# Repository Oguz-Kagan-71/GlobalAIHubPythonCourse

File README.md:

# GlobalAIHubPythonCourse
https://github.com/globalaihub/gaih-students-repo-example/blob/main/img/logo.png

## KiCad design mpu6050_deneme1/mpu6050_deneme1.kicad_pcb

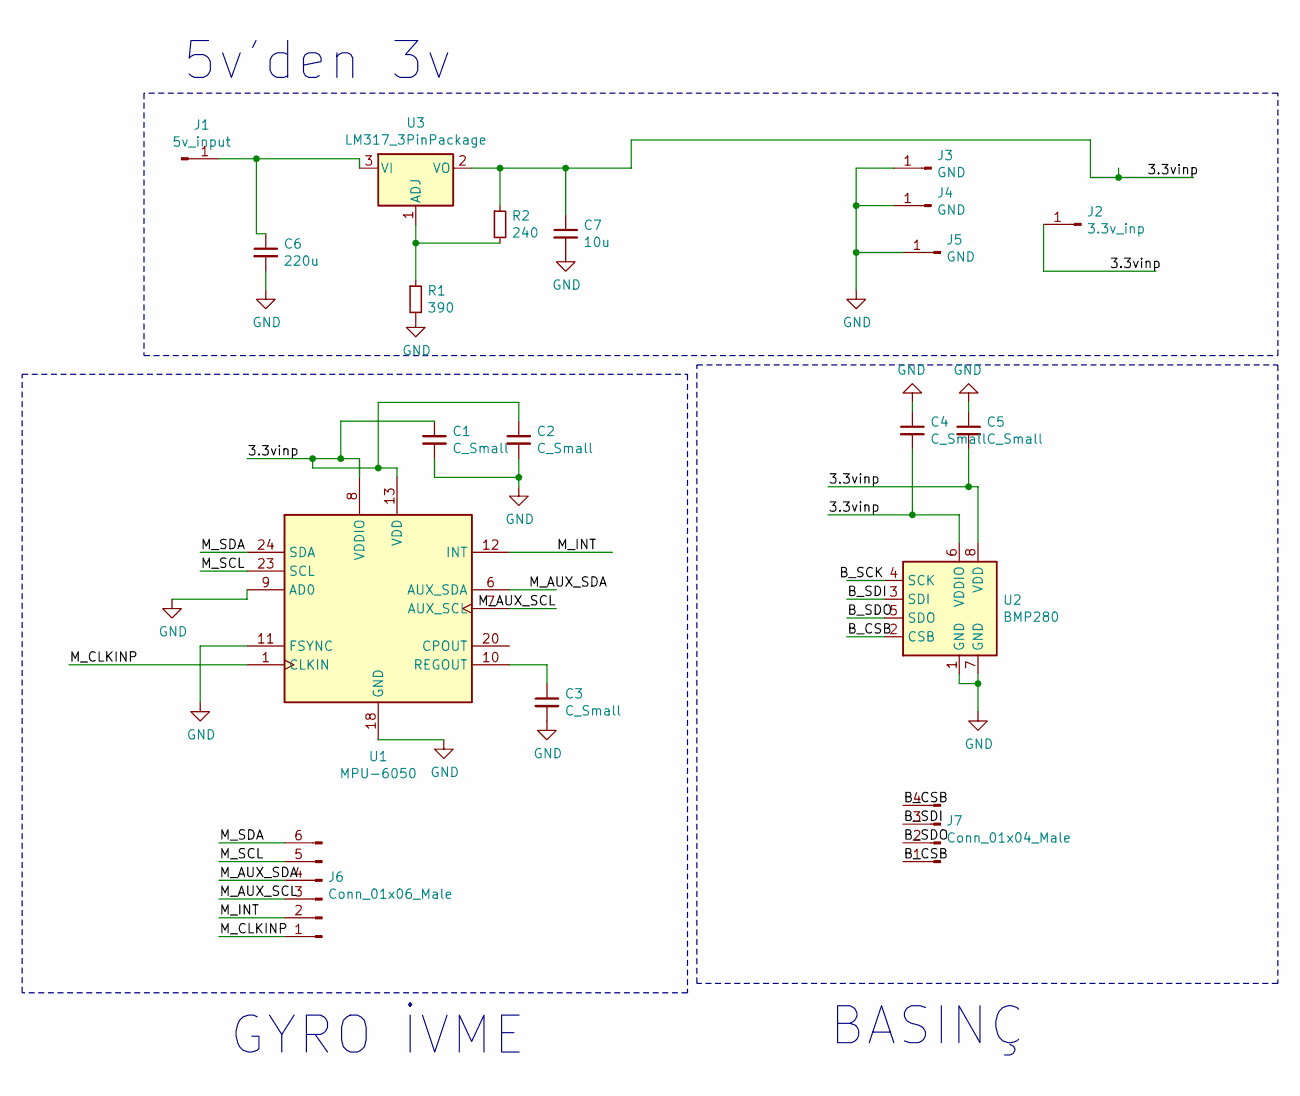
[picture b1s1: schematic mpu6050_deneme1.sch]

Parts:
C1, C2, C3, C4, C5: C_Small; CP_Elec_4x3
C6: 220u; CP_Elec_3x5.3
C7: 10u; CP_Elec_3x5.3
J1: 5v_input; PinHeader_1x01_P1.00mm_Vertical
J2: 3.3v_inp; PinHeader_1x01_P1.00mm_Horizontal
J3, J4, J5: GND; PinHeader_1x01_P1.00mm_Horizontal
J6: Conn_01x06_Male; PinHeader_1x06_P1.00mm_Vertical
J7: Conn_01x04_Male; PinHeader_1x04_P1.00mm_Vertical
R1: 390; R_0201_0603Metric
R2: 240; R_0201_0603Metric
U1: MPU-6050; InvenSense_QFN-24_4x4mm_P0.5mm
U2: BMP280; Bosch_LGA-8_2x2.5mm_P0.65mm_ClockwisePinNumbering
U3: LM317_3PinPackage; SOT-223-3_TabPin2

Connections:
/3.3vinp: C1.1, C2.1, C4.2, C5.2, C7.1, J2.1, R2.1, U1.8 (VDDIO), U1.13 (VDD), U2.6 (VDDIO), U2.8 (VDD), U3.2 (VO)
/B_CSB: J7.1, J7.4, U2.2 (CSB)
/B_SCK: U2.4 (SCK)
/B_SDI: J7.3, U2.3 (SDI)
/B_SDO: J7.2, U2.5 (SDO)
/M_AUX_SCL: J6.3, U1.7 (AUX_SCL)
/M_AUX_SDA: J6.4, U1.6 (AUX_SDA)
/M_CLKINP: J6.1, U1.1 (CLKIN)
/M_INT: J6.2, U1.12 (INT)
/M_SCL: J6.5, U1.23 (SCL)
/M_SDA: J6.6, U1.24 (SDA)
GND: C1.2, C2.2, C3.2, C4.1, C5.1, C6.2, C7.2, J3.1, J4.1, J5.1, R1.2, U1.9 (AD0), U1.11 (FSYNC), U1.18 (GND), U2.1 (GND), U2.7 (GND)
unnamed: C3.1, U1.10 (REGOUT)
unnamed: C6.1, J1.1, U3.3 (VI)
unnamed: R1.1, R2.2, U3.1 (ADJ)

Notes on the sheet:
5v'den 3v
GYRO İVME
BASINÇ

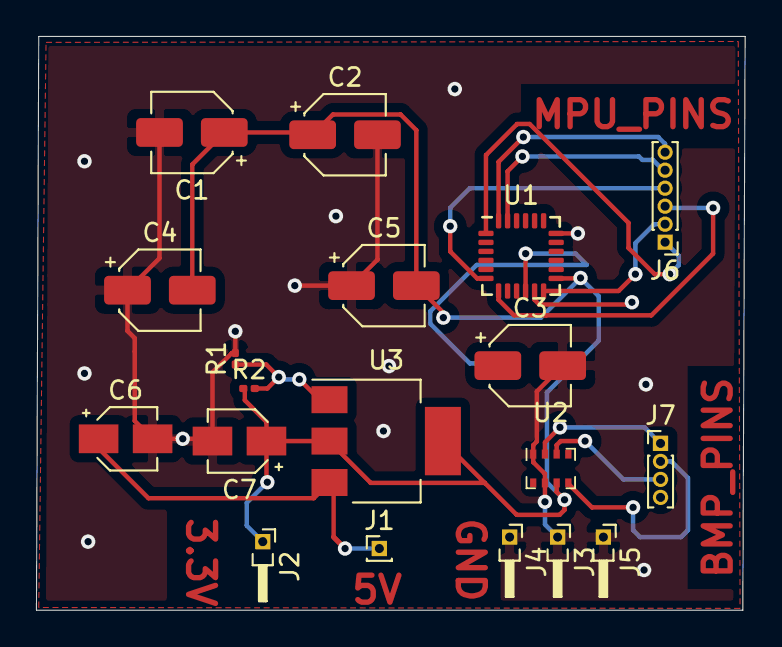
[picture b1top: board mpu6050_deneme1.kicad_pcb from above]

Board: 2 copper layers, 39.4 x 31.9 mm, 19 parts (0 on the bottom side), 14 nets.

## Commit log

2021-02-16 Create DENEME
2021-02-16 Create zartzurt
2021-02-21 Homework added
2021-07-26 Create mpu6050_deneme1.pro
    RND deneme
2021-07-26 added gnd layer and gnd via
2021-07-26 added vias and gnd zone
    added new vias and gnd zone. Old version haven`t vias and gnd layer
